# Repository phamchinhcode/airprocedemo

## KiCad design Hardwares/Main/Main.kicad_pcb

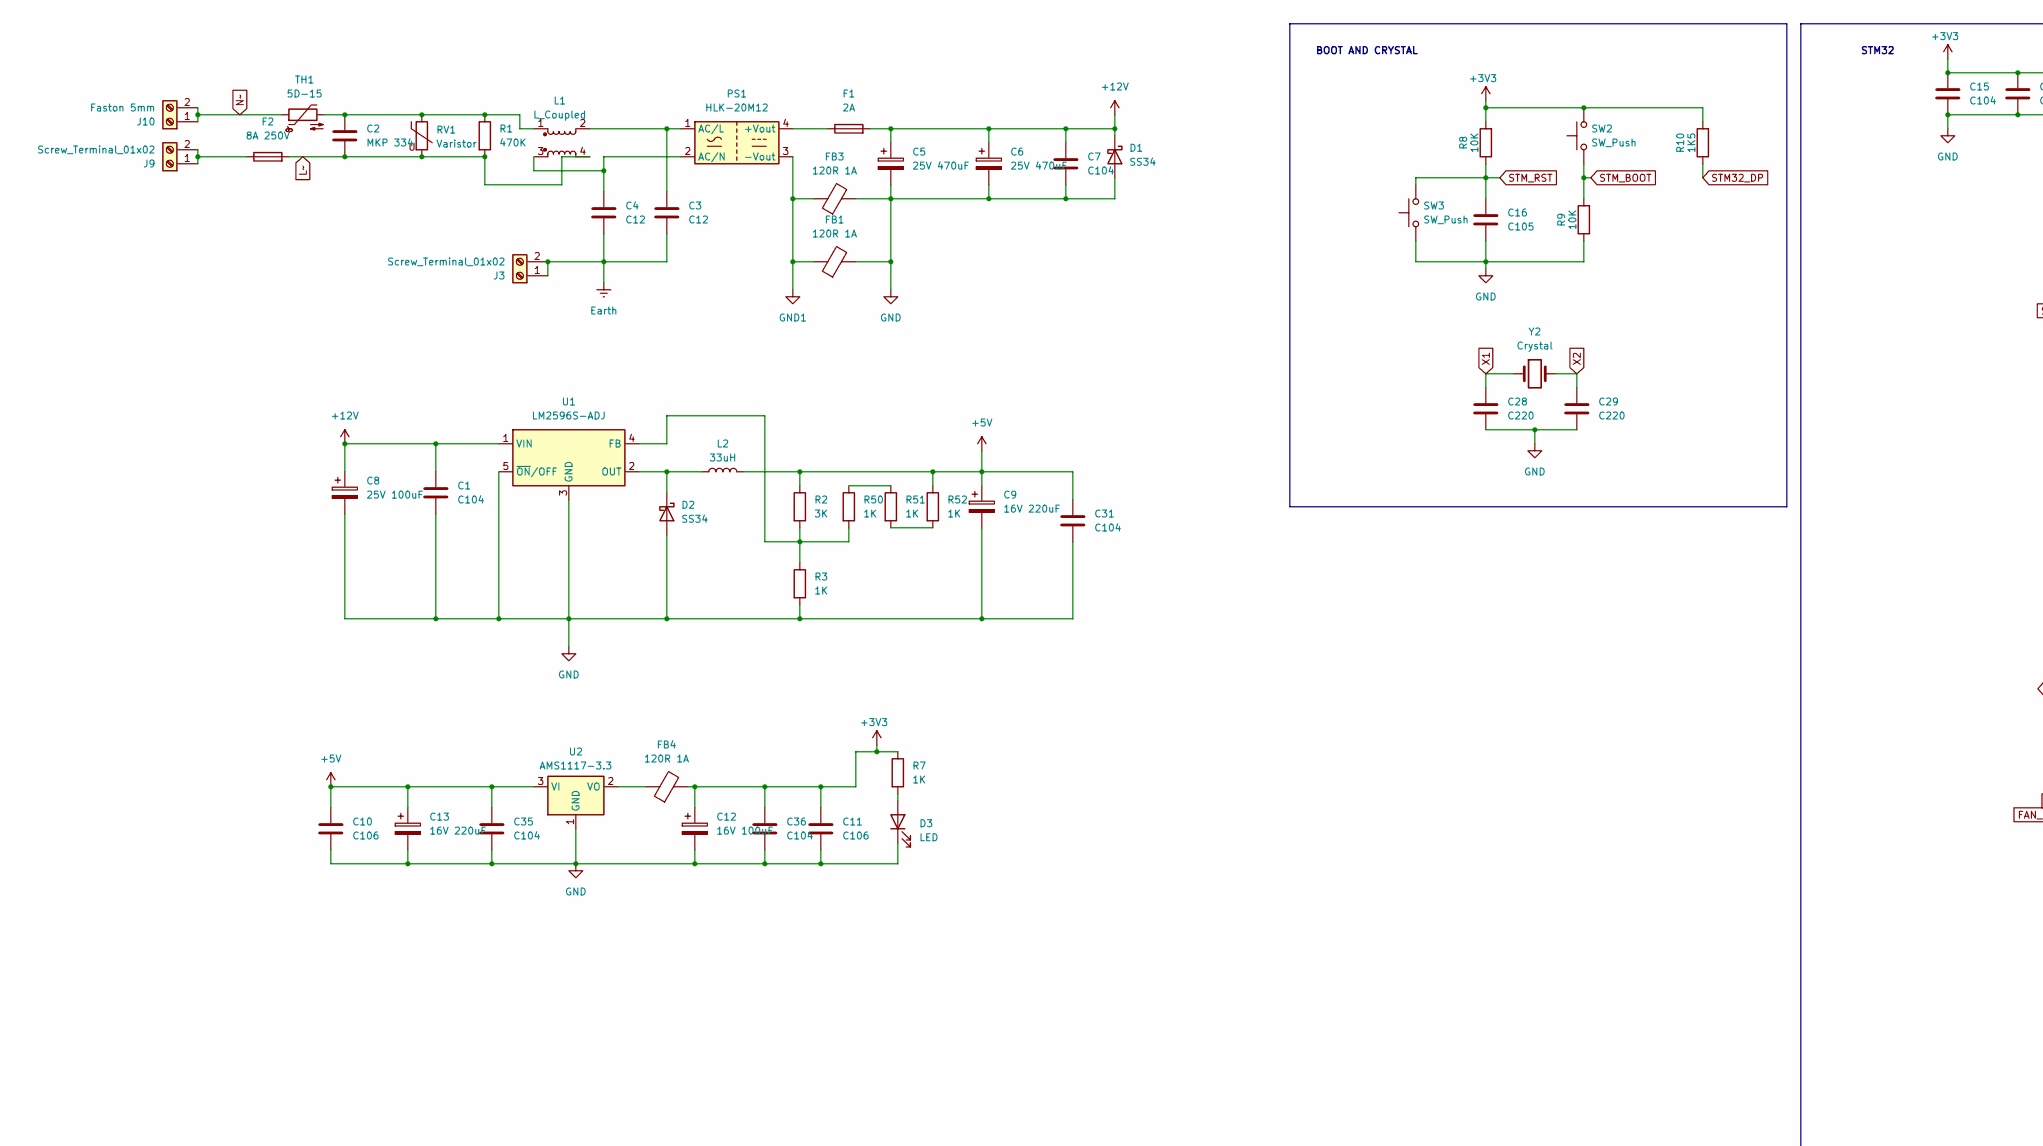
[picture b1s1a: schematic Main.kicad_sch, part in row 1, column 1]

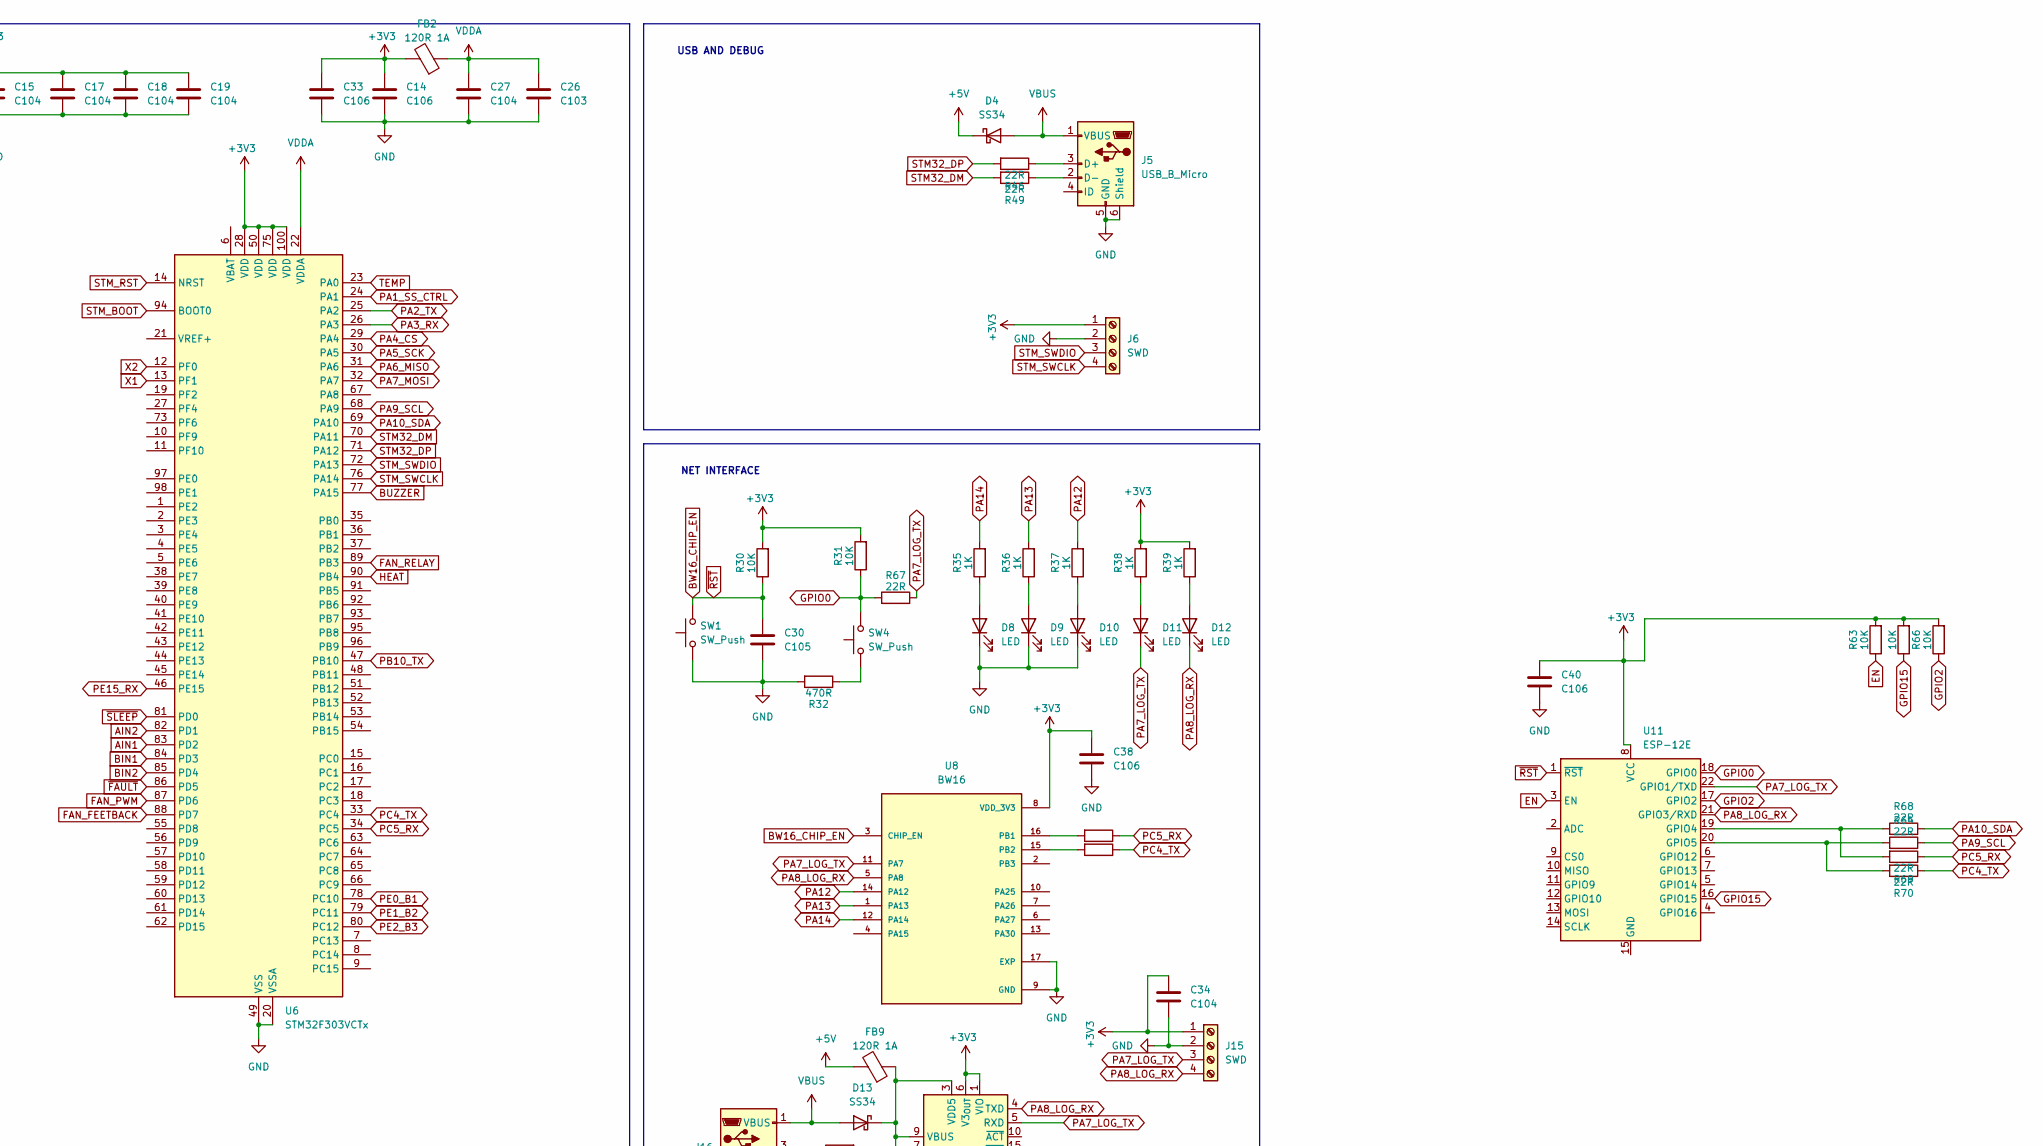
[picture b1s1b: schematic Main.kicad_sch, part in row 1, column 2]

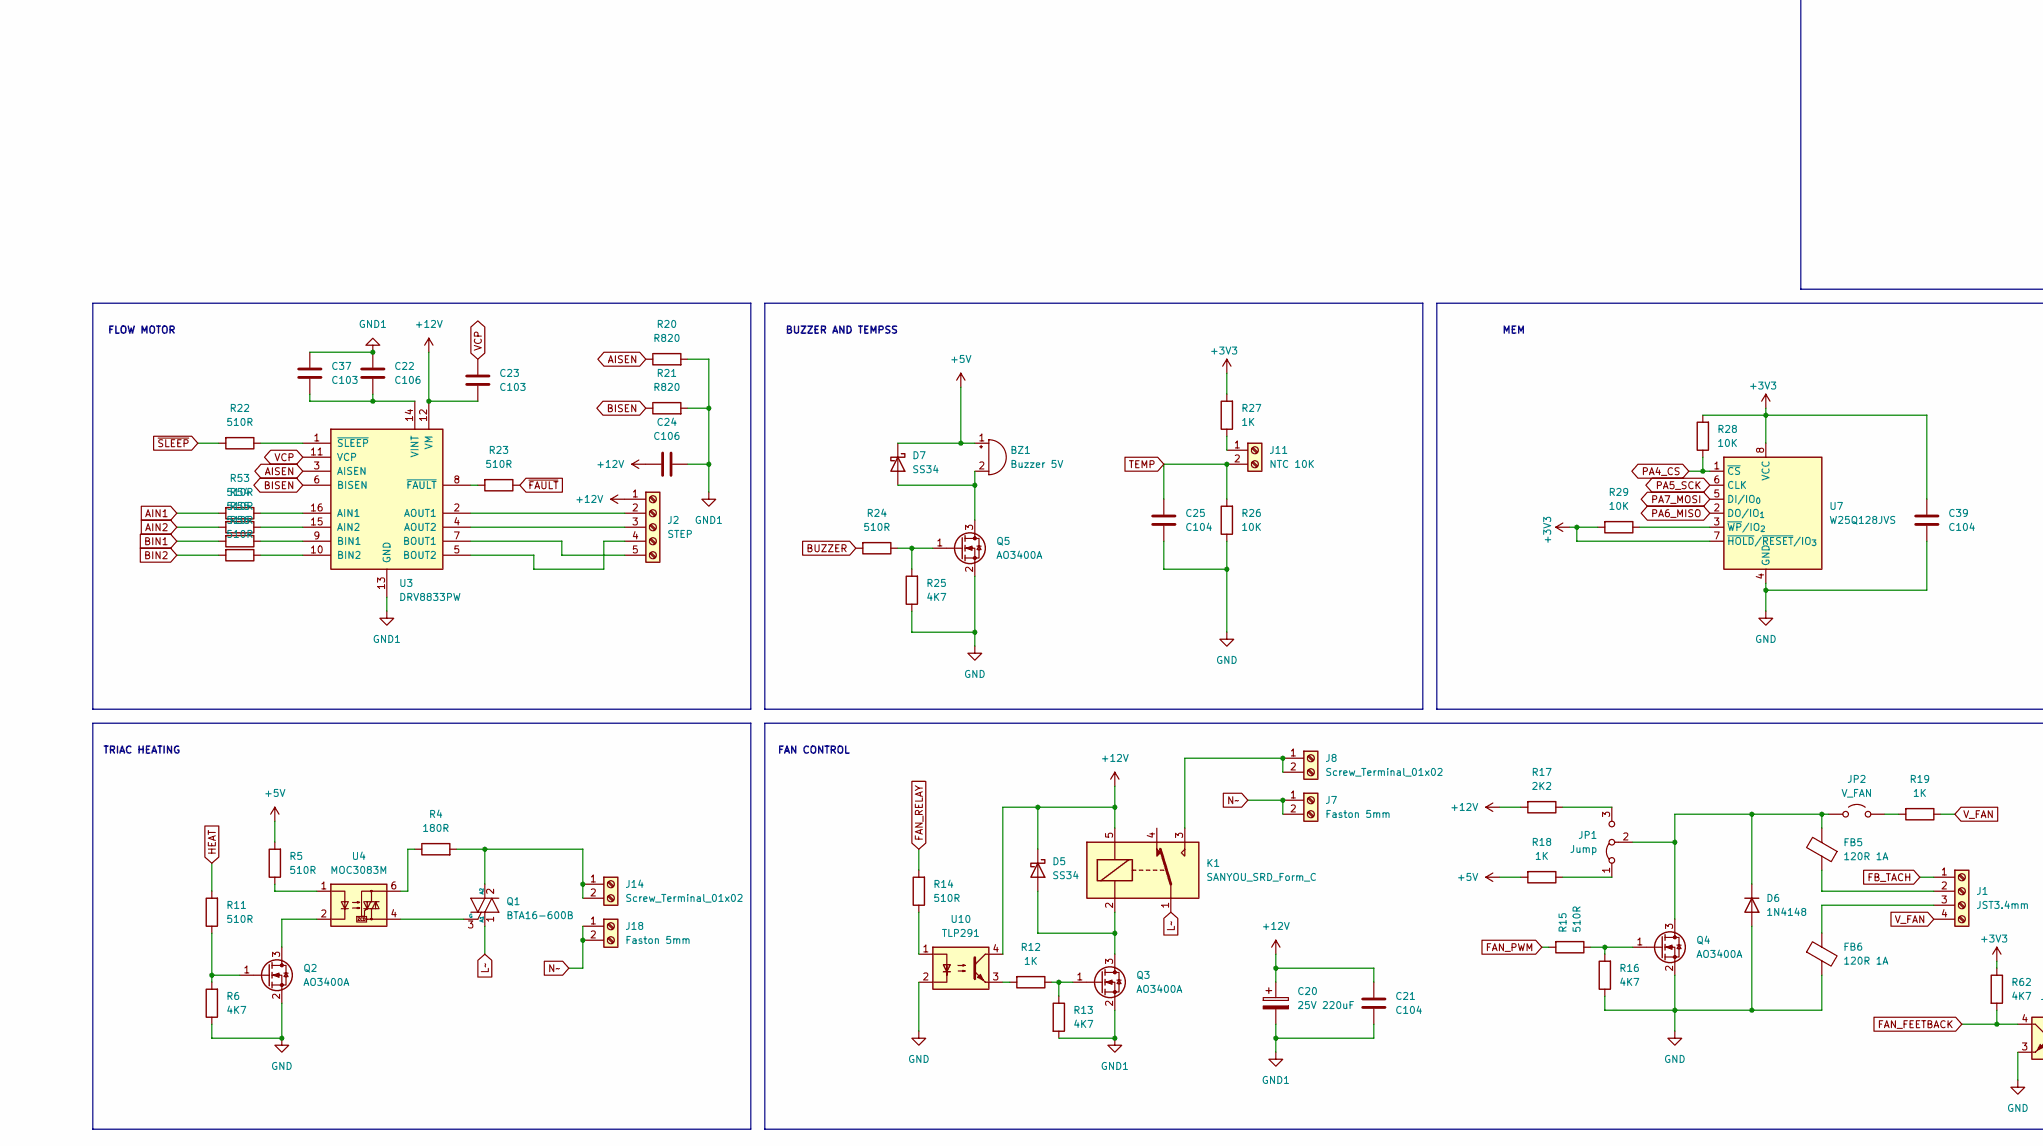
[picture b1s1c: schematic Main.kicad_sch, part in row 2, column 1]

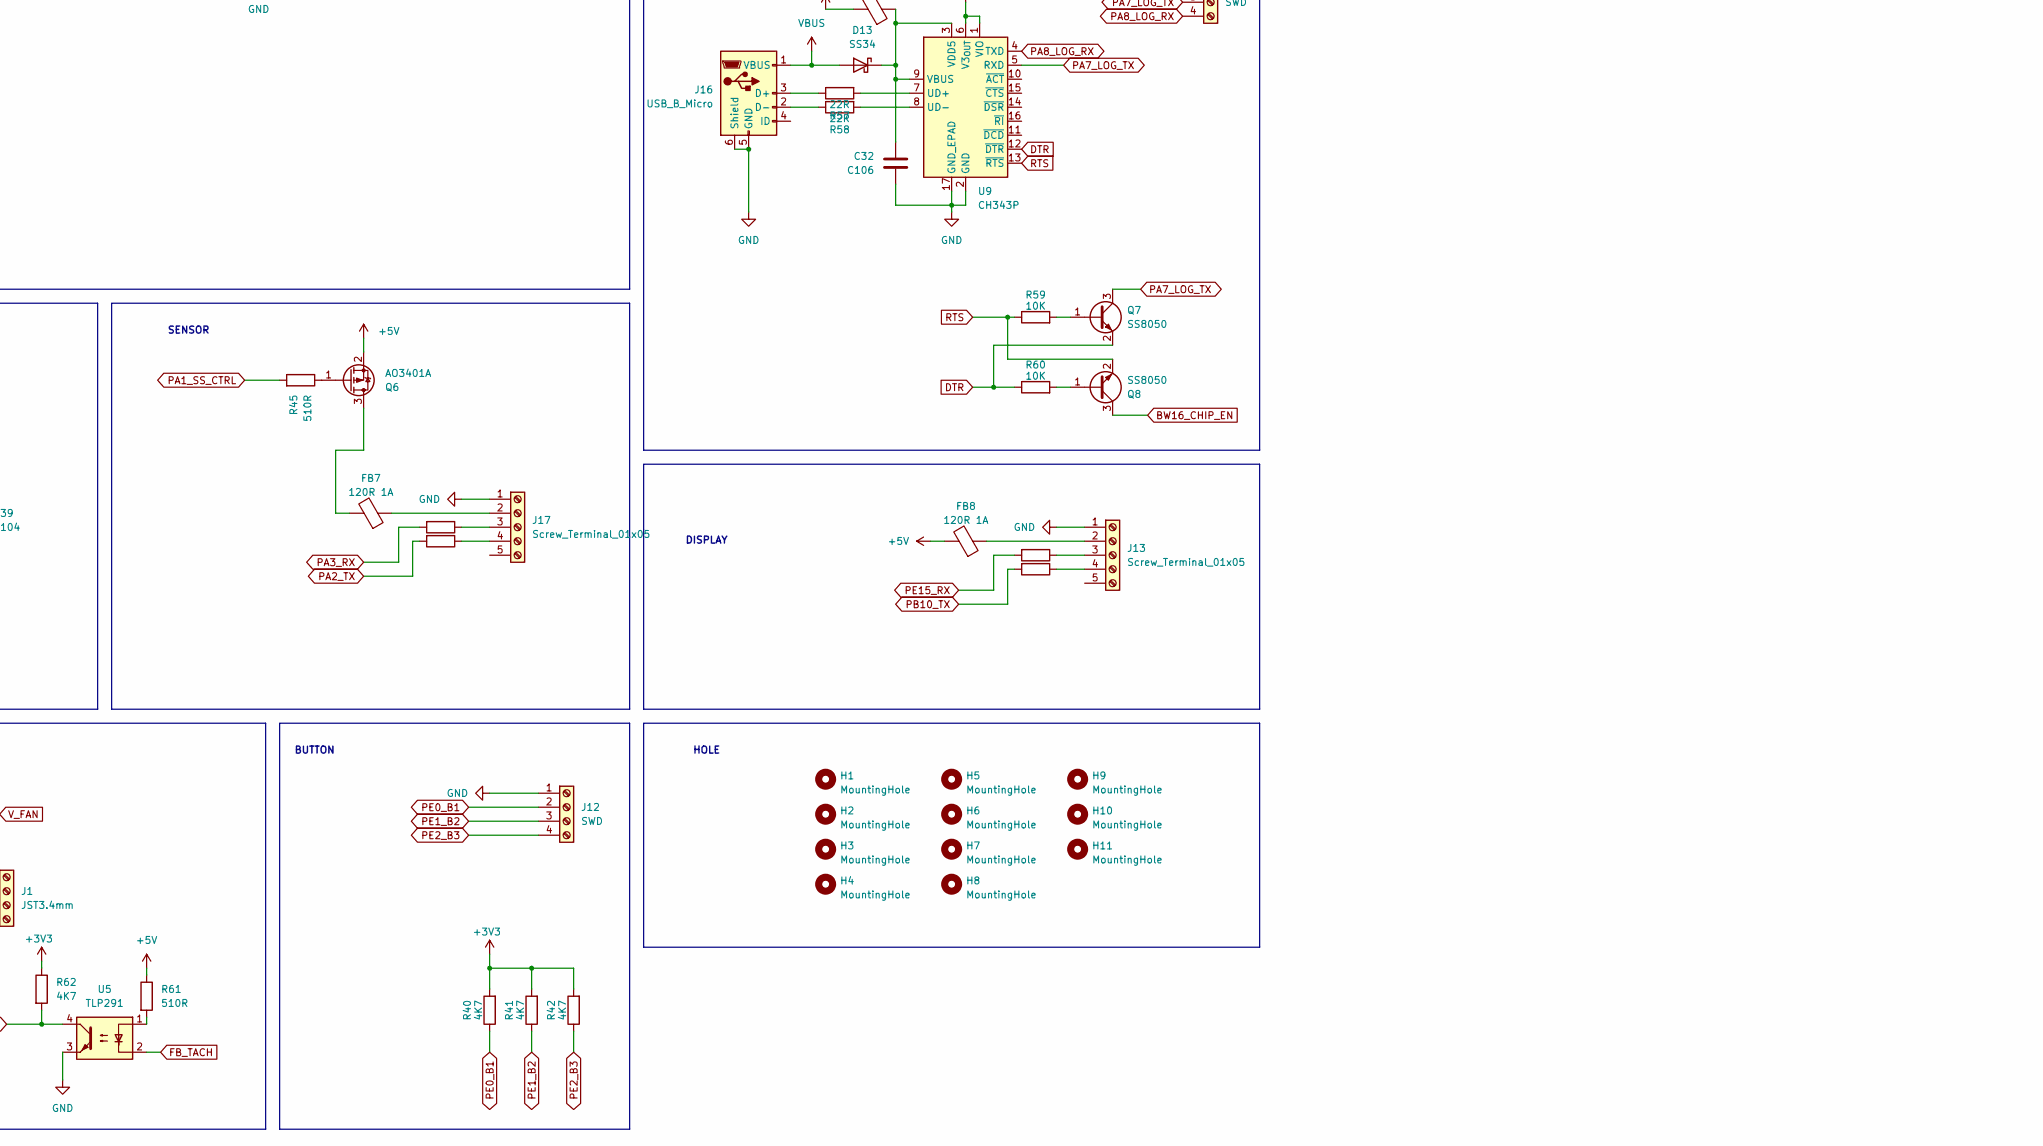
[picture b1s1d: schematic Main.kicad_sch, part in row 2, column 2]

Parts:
BZ1: Buzzer 5V; Buzzer_12x9.5RM7.6
C1, C7, C15, C17, C18, C19, C21, C25, C27, C31, C34, C35, C36, C39: C104; C_0805_2012Metric
C2: MKP 334; C_Rect_L18.0mm_W9.0mm_P15.00mm_FKS3_FKP3
C3, C4: C12; C_Disc_D7.5mm_W5.0mm_P7.50mm
C5, C6: 25V 470uF; CP_Radial_D8.0mm_P2.50mm
C8: 25V 100uF; CP_Radial_D8.0mm_P2.50mm
C9, C13: 16V 220uF; CP_Radial_D8.0mm_P2.50mm
C10, C11, C14, C22, C24, C32, C33, C38, C40: C106; C_1210_3225Metric
C12: 16V 100uF; CP_Radial_D8.0mm_P2.50mm
C16, C30: C105; C_0805_2012Metric
C20: 25V 220uF; CP_Radial_D8.0mm_P2.50mm
C23, C26, C37: C103; C_0805_2012Metric
C28, C29: C220; C_0805_2012Metric
D1, D2, D4, D5, D7, D13: SS34; D_SMA
D3, D8, D9, D10, D11, D12: LED; LED_0805_2012Metric
D6: 1N4148; D_DO-35_SOD27_P7.62mm_Horizontal
F1: 2A; Fuseholder_Clip-5x20mm_Eaton_1A5601-01_Inline_P20.80x6.76mm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
F2: 8A 250V; Fuseholder_Clip-5x20mm_Eaton_1A5601-01_Inline_P20.80x6.76mm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
FB1, FB3, FB4: 120R 1A; L_1210_3225Metric
FB2, FB5, FB6, FB7, FB8, FB9: 120R 1A; L_0805_2012Metric
H1, H2, H3, H4, H5, H6, H7, H8, H9, H10, H11: MountingHole; MountingHole_3.2mm_M3_DIN965
J1: JST3.4mm; TerminalBlock_MetzConnect_Type086_RT03404HBLC_1x04_P3.81mm_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
J2: STEP; Molex_KK-254_AE-6410-05A_1x05_P2.54mm_Vertical
J3, J8, J9, J14: Screw_Terminal_01x02; TerminalBlock_Phoenix_MKDS-1,5-2-5.08_1x02_P5.08mm_Horizont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
J5, J16: USB_B_Micro; USB_Micro-B_Wuerth_629105150521
J6, J12, J15: SWD; Molex_KK-254_AE-6410-04A_1x04_P2.54mm_Vertical
J7, J10, J18: Faston 5mm; TerminalBlock_Phoenix_MKDS-1,5-2-5.08_1x02_P5.08mm_Horizont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
J11: NTC 10K; Molex_KK-254_AE-6410-02A_1x02_P2.54mm_Vertical
J13, J17: Screw_Terminal_01x05; Molex_KK-254_AE-6410-05A_1x05_P2.54mm_Vertical
JP1: Jump; SolderJumper-3_P1.3mm_Bridged12_RoundedPad1.0x1.5mm_NumberL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
JP2: V_FAN; SolderJumper-2_P1.3mm_Open_RoundedPad1.0x1.5mm
K1: SANYOU_SRD_Form_C; Relay_SPDT_SANYOU_SRD_Series_Form_C
L1: L_Coupled; Untitled
L2: 33uH; L_Coilcraft_MSS1260H-XXX
PS1: HLK-20M12; Converter_ACDC_Hi-Link_HLK-20Mxx
Q1: BTA16-600B; TO-220-3_Vertical
Q2, Q3, Q4, Q5: AO3400A; SOT-23
Q6: AO3401A; SOT-23
Q7, Q8: SS8050; SOT-23-3
R1: 470K; R_1210_3225Metric
R2: 3K; R_0805_2012Metric
R3, R7, R12, R18, R19, R27, R35, R36, R37, R38, R39, R50, R51, R52: 1K; R_0805_2012Metric
R4: 180R; R_1210_3225Metric
R5, R11, R14, R15, R22, R23, R24, R45, R53, R54, R55, R56, R61: 510R; R_0805_2012Metric
R6, R13, R16, R25, R40, R41, R42, R62: 4K7; R_0805_2012Metric
R8, R9, R26, R28, R29, R30, R31, R59, R60, R63, R65, R66: 10K; R_0805_2012Metric
R10: 1K5; R_0805_2012Metric
R17: 2K2; R_0805_2012Metric
R20, R21: R820; R_1206_3216Metric
R32: 470R; R_0805_2012Metric
R33, R34, R43, R44, R47, R48: 0R; R_0805_2012Metric
R46, R49, R57, R58, R64, R67, R68, R69, R70: 22R; R_0805_2012Metric
RV1: Varistor; RV_Disc_D15.5mm_W4.2mm_P7.5mm
SW1, SW2, SW3, SW4: SW_Push; SW_SPST_TS-1088-xR025
TH1: 5D-15; RV_Disc_D15.5mm_W4.2mm_P7.5mm
U1: LM2596S-ADJ; TO-263-5_TabPin3
U2: AMS1117-3.3; SOT-223-3_TabPin2
U3: DRV8833PW; TSSOP-16_4.4x5mm_P0.65mm
U4: MOC3083M; DIP-6_W7.62mm_LongPads
U5, U10: TLP291; SOP-4_4.4x2.6mm_P1.27mm
U6: STM32F303VCTx; LQFP-100_14x14mm_P0.5mm
U7: W25Q128JVS; SOIC-8_5.3x5.3mm_P1.27mm
U8: BW16; MODULE_BW16; PARTREV V1.0
U9: CH343P; WCH_QFN-16-1EP_3x3mm_P0.5mm_EP1.8x1.8mm
U11: ESP-12E
Y2: Crystal; Crystal_HC49-4H_Vertical

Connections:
+3V3: C11.1, C12.1, C14.1, C15.1, C17.1, C18.1, C19.1, C33.1, C34.1, C36.1, C38.1, C39.1, C40.1, FB2.2, FB4.2, J6.1, J15.1, R7.1, R8.2, R10.2, R27.2, R28.2, R29.2, R30.2, R31.2, R38.2, R39.2, R40.2, R41.2, R42.2, R62.1, R63.2, R65.2, R66.2, SW2.2, U6.28 (VDD), U6.50 (VDD), U6.75 (VDD), U6.100 (VDD), U7.7 (~HOLD/~RESET/IO_{3}), U7.8 (VCC), U8.8 (VDD_3V3), U9.1 (VIO), U9.6 (V3_{OUT}), U11.8 (VCC)
+5V: BZ1.1 (+), C9.1, C10.1, C13.1, C31.1, C35.1, D4.1 (K), D7.1 (K), FB8.2, FB9.2, L2.2, Q6.2 (S), R2.1, R5.2, R18.2, R52.1, R61.1, U2.3 (VI)
+12V: C1.1, C5.1, C6.1, C7.1, C8.1, C20.1, C21.1, C23.2, C24.1, D1.1 (K), D5.1 (K), F1.2, J2.1, K1.5, R17.2, U1.1 (VIN), U3.12 (VM), U10.4
AIN1: R53.2, U6.83 (PD2)
AIN2: R54.2, U6.82 (PD1)
AISEN: R20.1, U3.3 (AISEN)
BIN1: R55.2, U6.84 (PD3)
BIN2: R56.2, U6.85 (PD4)
BISEN: R21.1, U3.6 (BISEN)
BUZZER: R24.2, U6.77 (PA15)
BW16_CHIP_EN: C30.1, Q8.3 (C), R30.1, SW1.2, U8.3 (CHIP_EN), U11.1 (~RST)
DTR: Q7.2 (E), R60.1, U9.12 (~DTR)
EN: R63.1, U11.3 (EN)
Earth: C3.2, C4.2, J3.1, J3.2
FAN_FEETBACK: R62.2, U5.4, U6.88 (PD7)
FAN_PWM: R15.2, U6.87 (PD6)
FAN_RELAY: R14.2, U6.89 (PB3)
FB_TACH: J1.1, U5.2
GND: C1.2, C5.2, C6.2, C7.2, C8.2, C9.2, C10.2, C11.2, C12.2, C13.2, C14.2, C15.2, C16.2, C17.2, C18.2, C19.2, C25.2, C26.2, C27.2, C28.2, C29.2, C30.2, C31.2, C32.2, C33.2, C34.2, C35.2, C36.2, C38.2, C39.2, C40.2, D1.2 (A), D2.2 (A), D3.1 (K), D6.2 (A), D8.1 (K), D9.1 (K), D10.1 (K), FB1.2, FB3.2, FB6.2, J5.5 (GND), J5.6 (Shield), J6.2, J12.1, J13.1, J15.2, J16.5 (GND), J16.6 (Shield), J17.1, Q2.2 (S), Q4.2 (S), Q5.2 (S), R3.2, R6.1, R9.1, R16.1, R25.1, R26.1, R32.2, SW1.1, SW3.1, U1.3 (GND), U1.5 (~ON/OFF), U2.1 (GND), U5.3, U6.20 (VSSA), U6.49 (VSS), U6.74 (VSS), U6.99 (VSS), U7.4 (GND), U8.9 (GND), U8.17 (EXP), U9.2 (GND), U9.17 (GND_EPAD), U10.2
GND1: C20.2, C21.2, C22.1, C24.2, C37.1, FB1.1, FB3.1, PS1.3 (-Vout), Q3.2 (S), R13.2, R20.2, R21.2, U3.13 (GND)
GPIO0: R31.1, R67.2, SW4.2, U11.18 (GPIO0)
GPIO2: R66.1, U11.17 (GPIO2)
GPIO15: R65.1, U11.16 (GPIO15)
HEAT: R11.2, U6.90 (PB4)
L~: C2.2, F2.2, K1.1, L1.4, Q1.1 (A1), R1.2, RV1.2
unnamed: BZ1.2 (-), D7.2 (A), Q5.3 (D)
unnamed: C2.1, L1.1, R1.1, RV1.1, TH1.2
unnamed: D2.1 (K), L2.1, U1.2 (OUT)
unnamed: D3.2 (A), R7.2
unnamed: D5.2 (A), K1.2, Q3.3 (D)
unnamed: D6.1 (K), FB5.2, JP1.2 (C), JP2.1 (A), Q4.3 (D)
unnamed: D8.2 (A), R35.1
unnamed: D9.2 (A), R36.1
unnamed: D10.2 (A), R37.1
unnamed: D11.2 (A), R38.1
unnamed: D12.2 (A), R39.1
unnamed: C32.1, D13.1 (K), FB9.1, U9.3 (VDD5), U9.9 (VBUS)
unnamed: FB5.1, J1.2
unnamed: FB6.1, J1.3
unnamed: J2.2, U3.2 (AOUT1)
unnamed: J2.3, U3.4 (AOUT2)
unnamed: J2.4, U3.5 (BOUT2)
unnamed: J2.5, U3.7 (BOUT1)
unnamed: J5.3 (D+), R46.1
unnamed: J5.2 (D-), R49.1
unnamed: J8.1, J8.2, K1.3
unnamed: F2.1, J9.1, J9.2
unnamed: J11.1, R27.1
unnamed: FB8.1, J13.2
unnamed: J13.3, R47.1
unnamed: J13.4, R48.1
unnamed: J14.1, J14.2, Q1.2 (A2), R4.2
unnamed: J16.3 (D+), R57.1
unnamed: J16.2 (D-), R58.1
unnamed: FB7.1, J17.2
unnamed: J17.3, R43.1
unnamed: J17.4, R44.1
unnamed: JP1.1 (A), R18.1
unnamed: JP1.3 (B), R17.1
unnamed: JP2.2 (B), R19.2
unnamed: F1.1, PS1.4 (+Vout)
unnamed: C3.1, L1.2, PS1.1 (AC/L)
unnamed: C4.1, L1.3, PS1.2 (AC/N)
unnamed: Q1.3 (G), U4.4
unnamed: Q2.3 (D), U4.2
unnamed: Q2.1 (G), R6.2, R11.1
unnamed: Q3.1 (G), R12.1, R13.1
unnamed: Q4.1 (G), R15.1, R16.2
unnamed: Q5.1 (G), R24.1, R25.2
unnamed: FB7.2, Q6.3 (D)
unnamed: Q6.1 (G), R45.1
unnamed: Q7.1 (B), R59.2
unnamed: Q8.1 (B), R60.2
unnamed: R4.1, U4.6
unnamed: R5.1, U4.1
unnamed: R12.2, U10.3
unnamed: R14.1, U10.1
unnamed: R32.1, SW4.1
unnamed: R50.1, R51.1
unnamed: R51.2, R52.2
unnamed: R61.2, U5.1
unnamed: R2.2, R3.1, R50.2, U1.4 (FB)
unnamed: FB4.1, U2.2 (VO)
unnamed: R53.1, U3.16 (AIN1)
unnamed: R54.1, U3.15 (AIN2)
unnamed: R55.1, U3.9 (BIN1)
unnamed: R56.1, U3.10 (BIN2)
unnamed: C22.2, C37.2, U3.14 (VINT)
unnamed: R23.2, U3.8 (~FAULT)
unnamed: R22.1, U3.1 (~SLEEP)
unnamed: R29.1, U7.3 (~WP/IO_{2})
unnamed: R33.2, U8.16 (PB1)
unnamed: R34.2, U8.15 (PB2)
unnamed: R57.2, U9.7 (UD+)
unnamed: R58.2, U9.8 (UD-)
unnamed: R68.2, R69.2, U11.19 (GPIO4)
unnamed: R64.2, R70.2, U11.20 (GPIO5)
N~: J7.1, J7.2, J10.1, J10.2, J18.1, J18.2, TH1.1
PA1_SS_CTRL: R45.2, U6.24 (PA1)
PA2_TX: R44.2, U6.25 (PA2)
PA3_RX: R43.2, U6.26 (PA3)
PA4_CS: R28.1, U6.29 (PA4), U7.1 (~CS)
PA5_SCK: U6.30 (PA5), U7.6 (CLK)
PA6_MISO: U6.31 (PA6), U7.2 (DO/IO_{1})
PA7_LOG_TX: D11.1 (K), J15.3, Q7.3 (C), R67.1, U8.11 (PA7), U9.5 (RXD), U11.22 (GPIO1/TXD)
PA7_MOSI: U6.32 (PA7), U7.5 (DI/IO_{0})
PA8_LOG_RX: D12.1 (K), J15.4, U8.5 (PA8), U9.4 (TXD), U11.21 (GPIO3/RXD)
PA9_SCL: R64.1, U6.68 (PA9)
PA10_SDA: R68.1, U6.69 (PA10)
PA12: R37.2, U8.14 (PA12)
PA13: R36.2, U8.1 (PA13)
PA14: R35.2, U8.12 (PA14)
PB10_TX: R48.2, U6.47 (PB10)
PC4_TX: R34.1, R70.1, U6.33 (PC4)
PC5_RX: R33.1, R69.1, U6.34 (PC5)
PE0_B1: J12.2, R40.1, U6.78 (PC10)
PE1_B2: J12.3, R41.1, U6.79 (PC11)
PE2_B3: J12.4, R42.1, U6.80 (PC12)
PE15_RX: R47.2, U6.46 (PE15)
RTS: Q8.2 (E), R59.1, U9.13 (~RTS)
STM32_DM: R49.2, U6.70 (PA11)
STM32_DP: R10.1, R46.2, U6.71 (PA12)
STM_BOOT: R9.2, SW2.1, U6.94 (BOOT0)
STM_RST: C16.1, R8.1, SW3.2, U6.14 (NRST)
STM_SWCLK: J6.4, U6.76 (PA14)
STM_SWDIO: J6.3, U6.72 (PA13)
TEMP: C25.1, J11.2, R26.2, U6.23 (PA0)
VBUS: D4.2 (A), D13.2 (A), J5.1 (VBUS), J16.1 (VBUS)
VCP: C23.1, U3.11 (VCP)
VDDA: C26.1, C27.1, FB2.1, U6.22 (VDDA)
V_FAN: J1.4, R19.1
X1: C28.1, U6.13 (PF1), Y2.1
X2: C29.1, U6.12 (PF0), Y2.2
~FAULT: R23.1, U6.86 (PD5)
~SLEEP: R22.2, U6.81 (PD0)

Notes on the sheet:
STM32
MEM
BUTTON
NET INTERFACE
BOOT AND CRYSTAL
HOLE
FAN CONTROL
BUZZER AND TEMPSS
FLOW MOTOR
SENSOR
USB AND DEBUG
TRIAC HEATING
DISPLAY

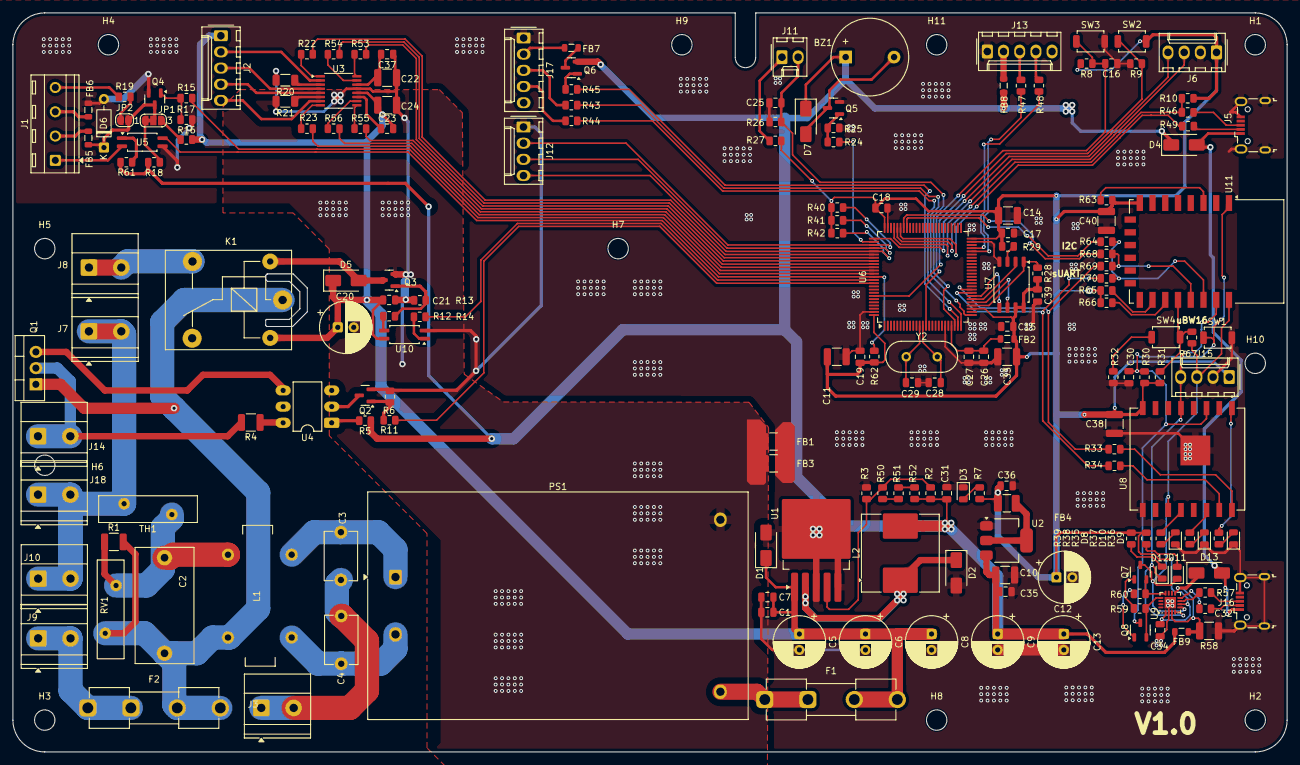
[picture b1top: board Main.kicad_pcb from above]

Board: 2 copper layers, 200.0 x 116.0 mm, 195 parts (0 on the bottom side), 135 nets.

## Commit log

2026-04-01 first update
2026-04-01 add file test
2026-04-01 update test
2026-04-01 update test1
2026-04-01 update test2
2026-04-01 update firmware
2026-04-01 add attribute
2026-04-01 add fw
2026-04-01 rm firmw
2026-04-01 add firmw
